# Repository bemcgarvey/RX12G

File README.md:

## RX12G  

Next generation of the RX12 receiver with built in gyro/stabilization  
Can be used with up to 3 DSMX satellite receivers or with any receiver that supports sBus output
(like the FrSky XSR or r-XSR receivers)  

Documentation will appear here once I complete it.

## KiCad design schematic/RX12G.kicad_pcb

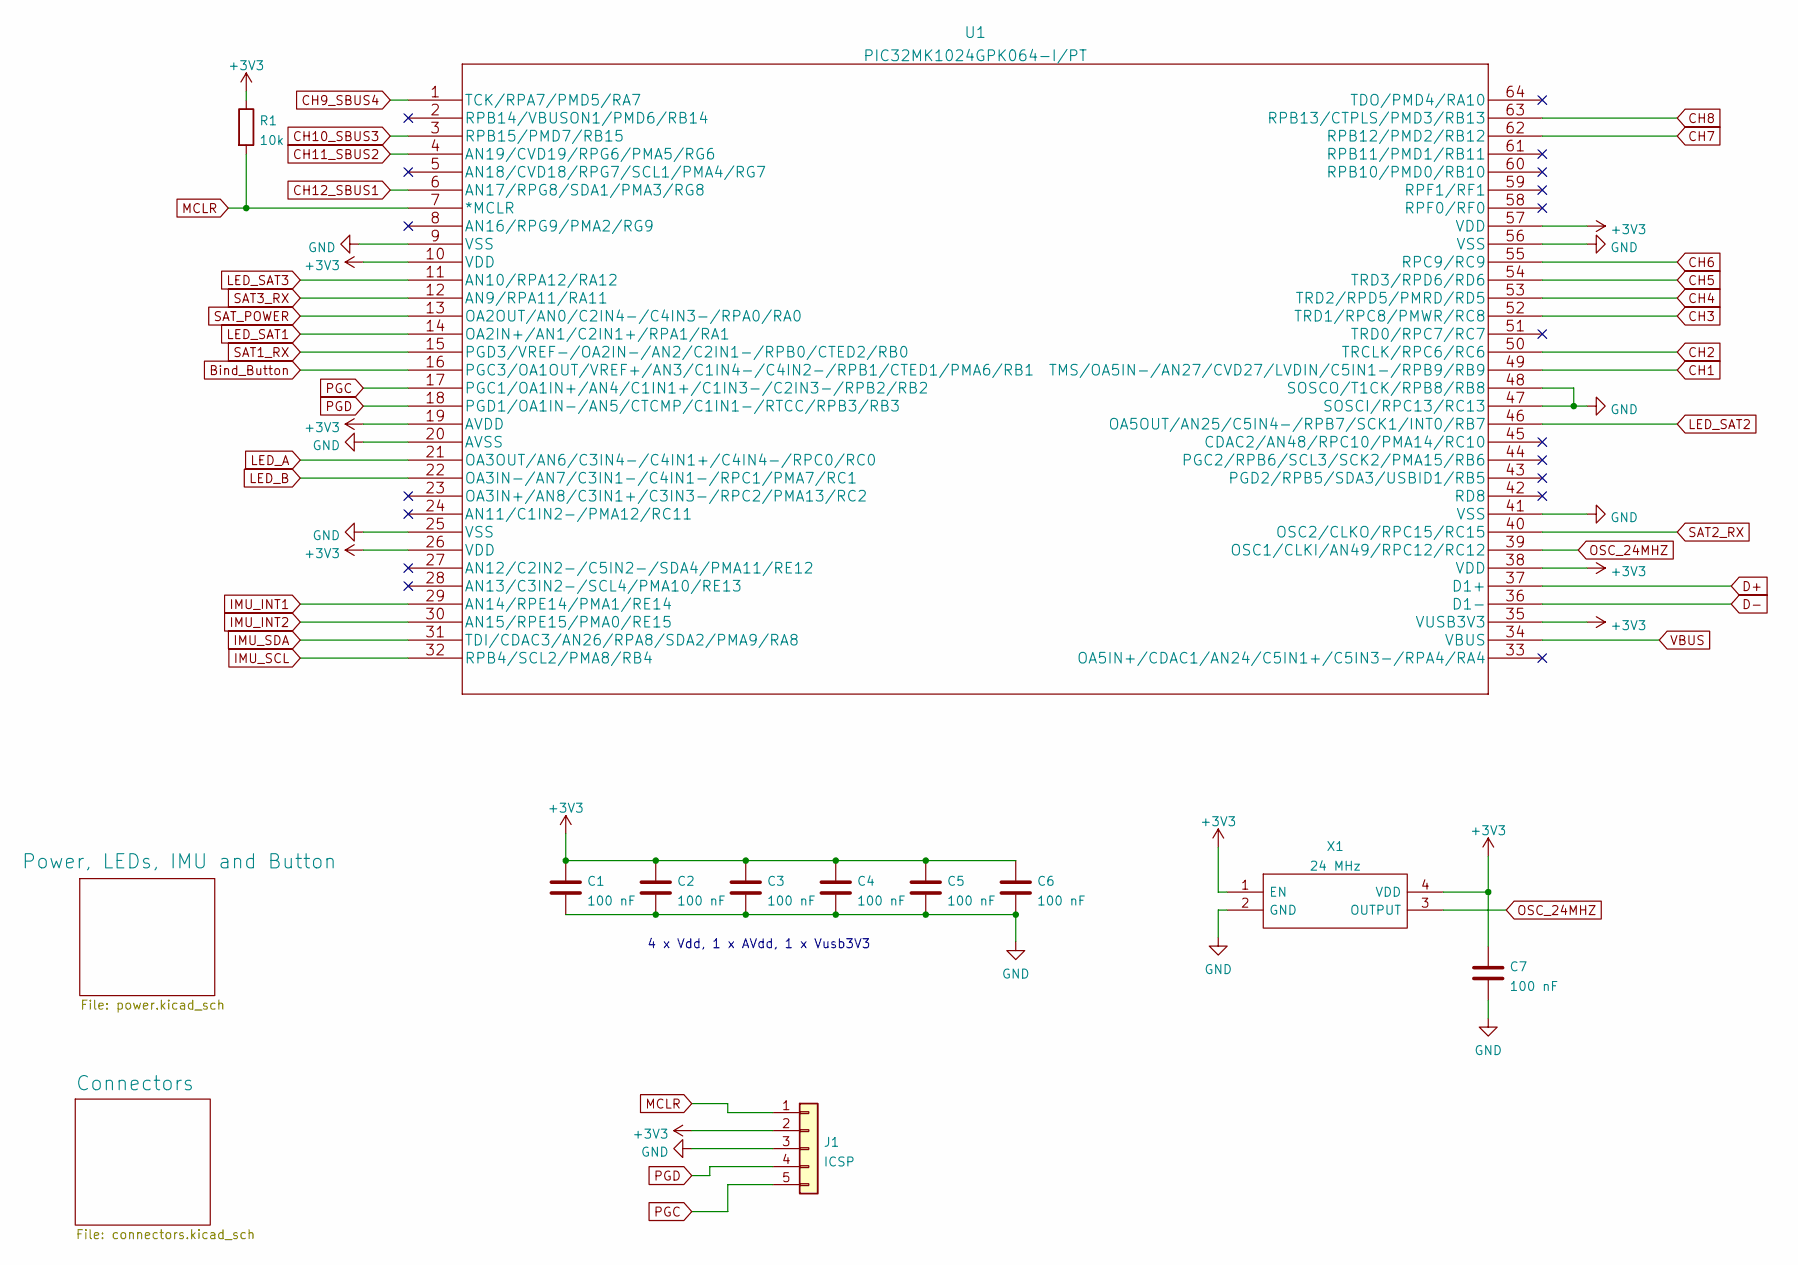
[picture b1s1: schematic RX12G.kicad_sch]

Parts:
C1, C2, C3, C4, C5, C6, C7: 100 nF; C_0402_1005Metric
J1: ICSP; PinHeader_1x05_P2.54mm_Vertical
R1: 10k; R_0603_1608Metric
U1: PIC32MK1024GPK064-I/PT; PIC32MK1024GPK064-I&slash_PT
X1: 24 MHz; ASTMUPCE3312000MHZLJET; Mouser Part Number 815-AMPMAFB-12.0000T

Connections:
+3V3: C1.1, C2.1, C3.1, C4.1, C5.1, C6.1, C7.1, J1.2, R1.1, U1.10 (VDD), U1.19 (AVDD), U1.26 (VDD), U1.35 (VUSB3V3), U1.38 (VDD), U1.57 (VDD), X1.1 (EN), X1.4 (VDD); also elsewhere on the board
Bind_Button: U1.16 (PGC3/OA1OUT/VREF+/AN3/C1IN4-/C4IN2-/RPB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); also elsewhere on the board
CH1: U1.49 (TMS/OA5IN-/AN27/CVD27/LVDIN/C5IN1-/RPB9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); also elsewhere on the board
CH2: U1.50 (TRCLK/RPC6/RC6); also elsewhere on the board
CH3: U1.52 (TRD1/RPC8/PMWR/RC8); also elsewhere on the board
CH4: U1.53 (TRD2/RPD5/PMRD/RD5); also elsewhere on the board
CH5: U1.54 (TRD3/RPD6/RD6); also elsewhere on the board
CH6: U1.55 (RPC9/RC9); also elsewhere on the board
CH7: U1.62 (RPB12/PMD2/RB12); also elsewhere on the board
CH8: U1.63 (RPB13/CTPLS/PMD3/RB13); also elsewhere on the board
CH9_SBUS4: U1.1 (TCK/RPA7/PMD5/RA7); also elsewhere on the board
CH10_SBUS3: U1.3 (RPB15/PMD7/RB15); also elsewhere on the board
CH11_SBUS2: U1.4 (AN19/CVD19/RPG6/PMA5/RG6); also elsewhere on the board
CH12_SBUS1: U1.6 (AN17/RPG8/SDA1/PMA3/RG8); also elsewhere on the board
D+: U1.37 (D1+); also elsewhere on the board
D-: U1.36 (D1-); also elsewhere on the board
GND: C1.2, C2.2, C3.2, C4.2, C5.2, C6.2, C7.2, J1.3, U1.9 (VSS), U1.20 (AVSS), U1.25 (VSS), U1.41 (VSS), U1.47 (SOSCI/RPC13/RC13), U1.48 (SOSCO/T1CK/RPB8/RB8), U1.56 (VSS), X1.2 (GND); also elsewhere on the board
IMU_INT1: U1.29 (AN14/RPE14/PMA1/RE14); also elsewhere on the board
IMU_INT2: U1.30 (AN15/RPE15/PMA0/RE15); also elsewhere on the board
IMU_SCL: U1.32 (RPB4/SCL2/PMA8/RB4); also elsewhere on the board
IMU_SDA: U1.31 (TDI/CDAC3/AN26/RPA8/SDA2/PMA9/RA8); also elsewhere on the board
LED_A: U1.21 (OA3OUT/AN6/C3IN4-/C4IN1+/C4IN4-/RPC0/RC0); also elsewhere on the board
LED_B: U1.22 (OA3IN-/AN7/C3IN1-/C4IN1-/RPC1/PMA7/RC1); also elsewhere on the board
LED_SAT1: U1.14 (OA2IN+/AN1/C2IN1+/RPA1/RA1); also elsewhere on the board
LED_SAT2: U1.46 (OA5OUT/AN25/C5IN4-/RPB7/SCK1/INT0/RB7); also elsewhere on the board
LED_SAT3: U1.11 (AN10/RPA12/RA12); also elsewhere on the board
MCLR: J1.1, R1.2, U1.7 (*MCLR)
OSC_24MHZ: U1.39 (OSC1/CLKI/AN49/RPC12/RC12), X1.3 (OUTPUT)
PGC: J1.5, U1.17 (PGC1/OA1IN+/AN4/C1IN1+/C1IN3-/C2IN3-/RP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)
PGD: J1.4, U1.18 (PGD1/OA1IN-/AN5/CTCMP/C1IN1-/RTCC/RPB3/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)
SAT1_RX: U1.15 (PGD3/VREF-/OA2IN-/AN2/C2IN1-/RPB0/CTED2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); also elsewhere on the board
SAT2_RX: U1.40 (OSC2/CLKO/RPC15/RC15); also elsewhere on the board
SAT3_RX: U1.12 (AN9/RPA11/RA11); also elsewhere on the board
SAT_POWER: U1.13 (OA2OUT/AN0/C2IN4-/C4IN3-/RPA0/RA0); also elsewhere on the board
VBUS: U1.34 (VBUS); also elsewhere on the board

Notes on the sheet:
4 x Vdd, 1 x AVdd, 1 x Vusb3V3

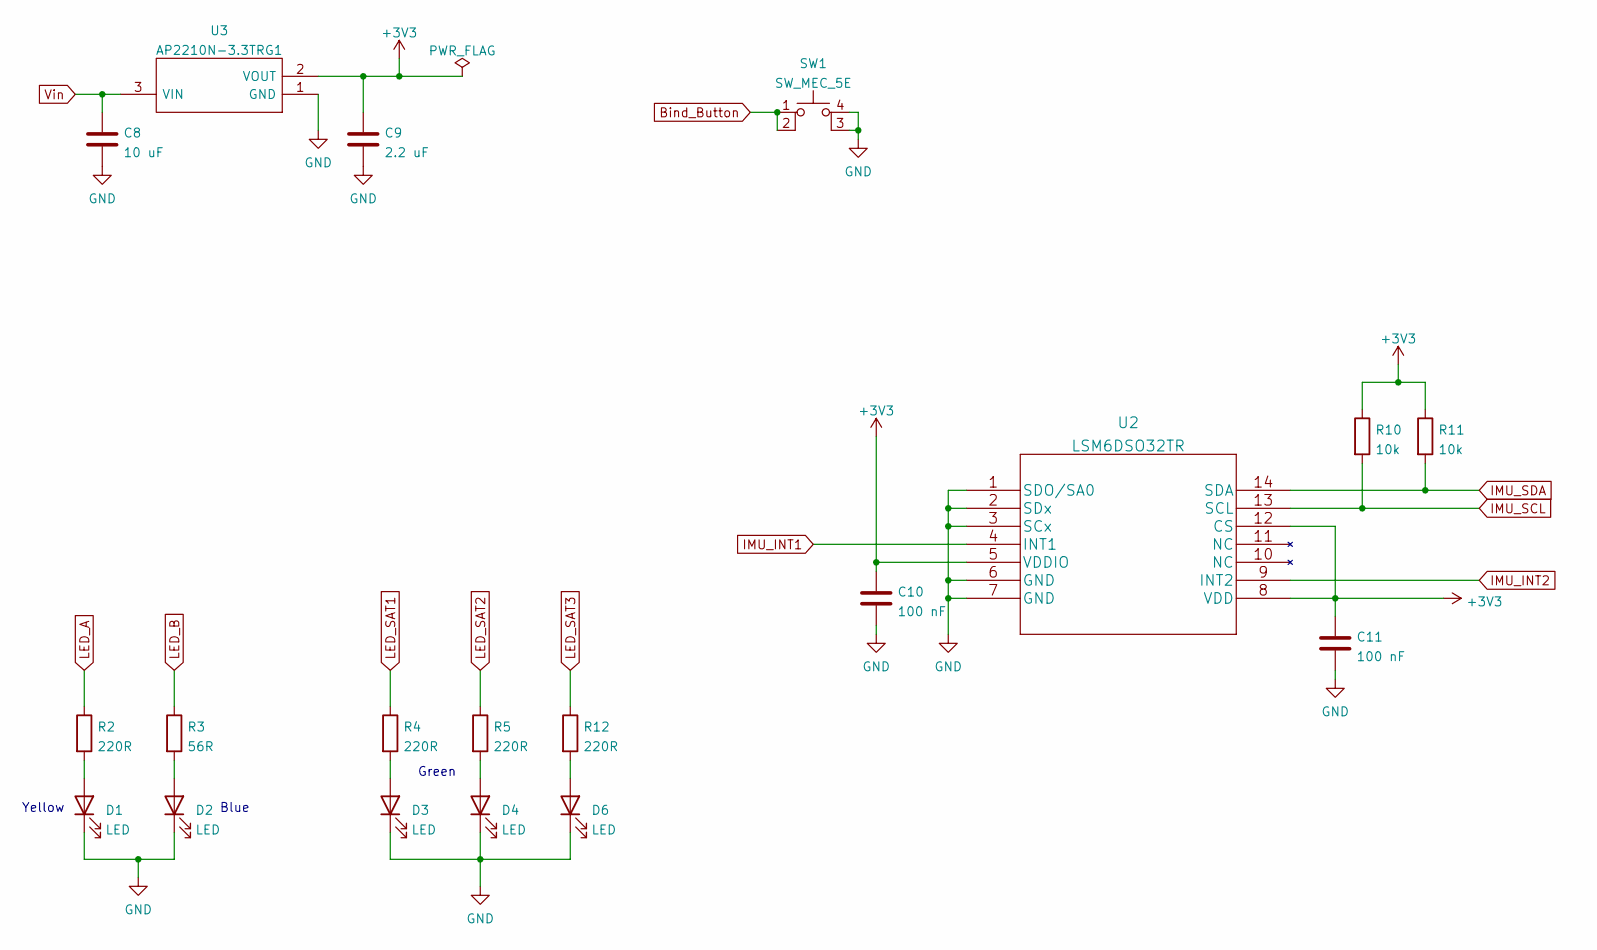
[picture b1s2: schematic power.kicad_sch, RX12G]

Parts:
C8: 10 uF; C_0603_1608Metric
C9: 2.2 uF; C_0603_1608Metric
C10, C11: 100 nF; C_0402_1005Metric
D1, D2, D3, D4, D6: LED; LED_0603_1608Metric
R2, R4, R5, R12: 220R; R_0603_1608Metric
R3: 56R; R_0603_1608Metric
R10, R11: 10k; R_0603_1608Metric
SW1: SW_MEC_5E; PTS647SK38SMTR2LFS
U2: LSM6DSO32TR
U3: AP2210N-3.3TRG1; SOT95P280X145-3N; Mouser Part Number 621-AP2210N-3.3TRG1

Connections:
+3V3: C9.1, C10.1, C11.1, R10.1, R11.1, U2.5 (VDDIO), U2.8 (VDD), U2.12 (CS), U3.2 (VOUT); also elsewhere on the board
Bind_Button: SW1.1, SW1.2; also elsewhere on the board
GND: C8.2, C9.2, C10.2, C11.2, D1.1 (K), D2.1 (K), D3.1 (K), D4.1 (K), D6.1 (K), SW1.3 (K), SW1.4 (A), U2.1 (SDO/SA0), U2.2 (SDx), U2.3 (SCx), U2.6 (GND), U2.7 (GND), U3.1 (GND); also elsewhere on the board
IMU_INT1: U2.4 (INT1); also elsewhere on the board
IMU_INT2: U2.9 (INT2); also elsewhere on the board
IMU_SCL: R10.2, U2.13 (SCL); also elsewhere on the board
IMU_SDA: R11.2, U2.14 (SDA); also elsewhere on the board
LED_A: R2.1; also elsewhere on the board
LED_B: R3.1; also elsewhere on the board
LED_SAT1: R4.1; also elsewhere on the board
LED_SAT2: R5.1; also elsewhere on the board
LED_SAT3: R12.1; also elsewhere on the board
unnamed: D1.2 (A), R2.2
unnamed: D2.2 (A), R3.2
unnamed: D3.2 (A), R4.2
unnamed: D4.2 (A), R5.2
unnamed: D6.2 (A), R12.2
Vin: C8.1, U3.3 (VIN); also elsewhere on the board

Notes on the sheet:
Blue
Yellow
Green

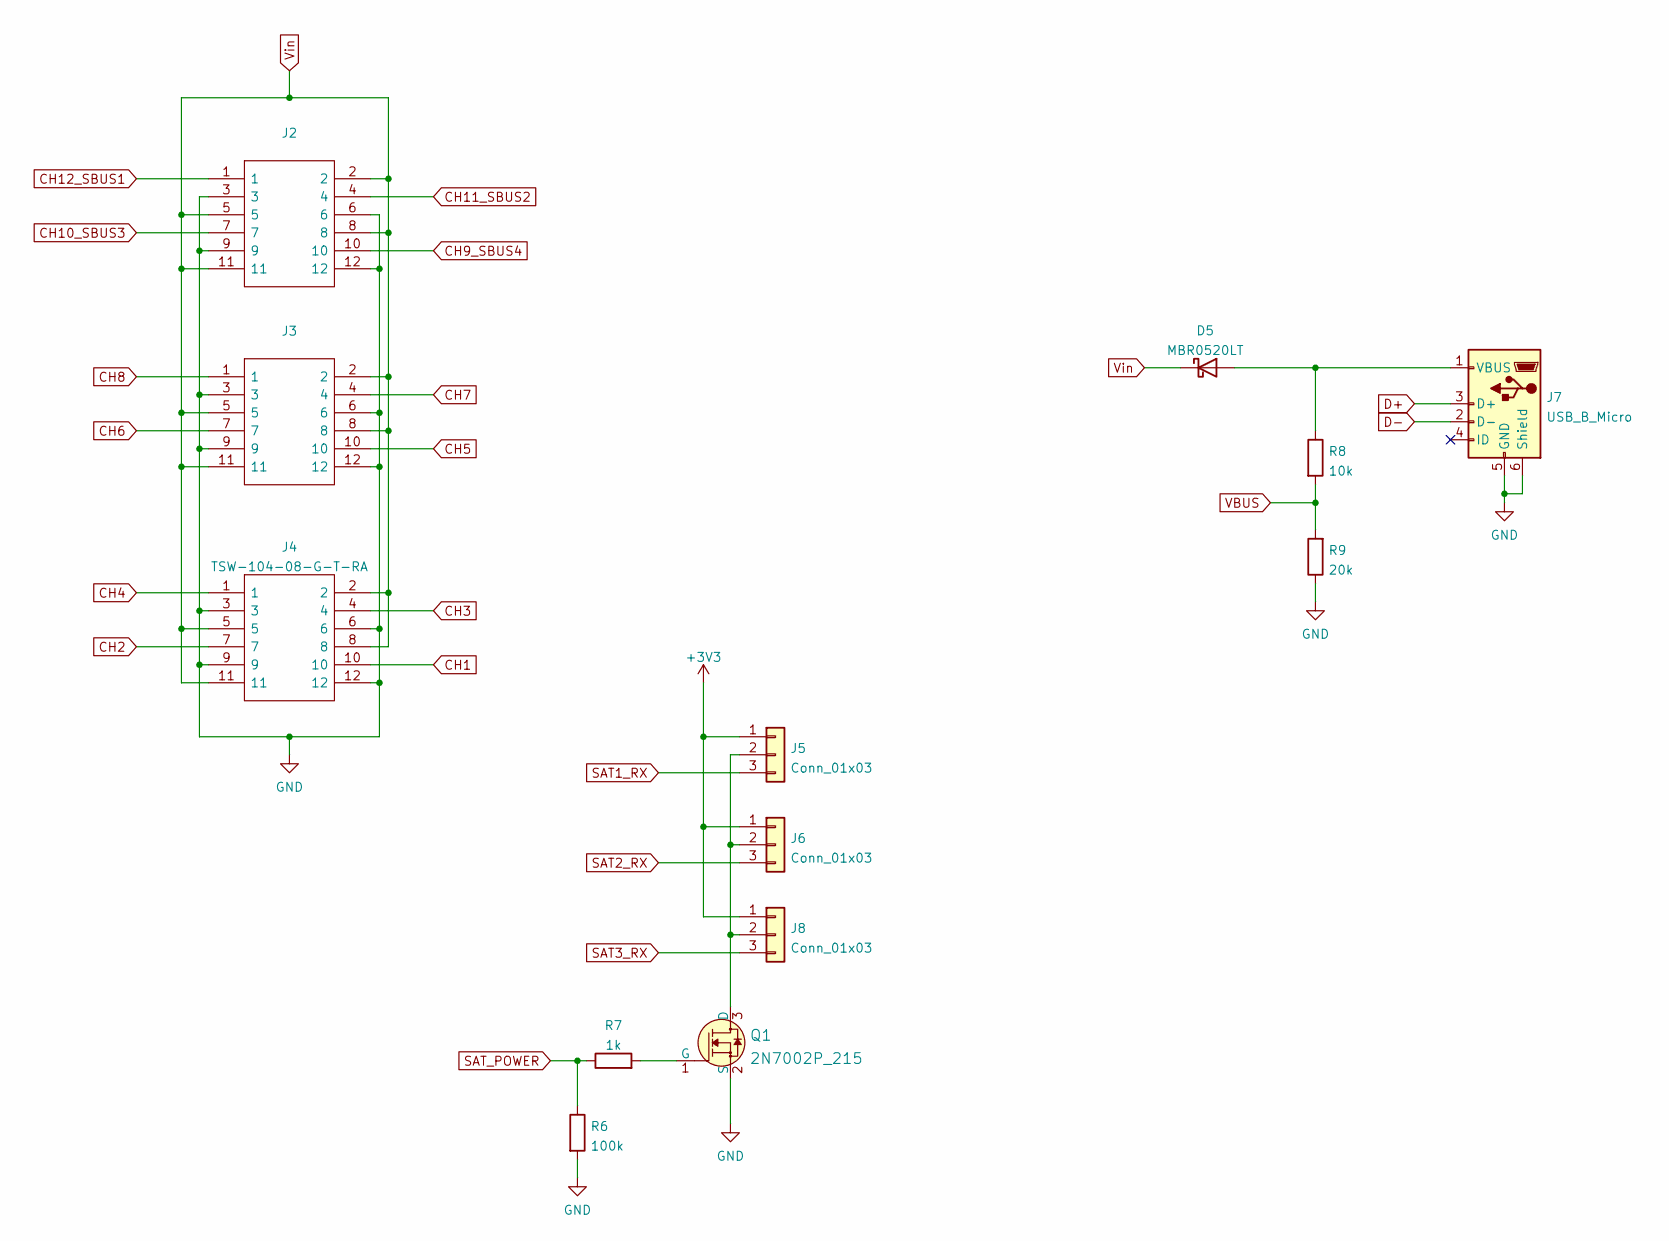
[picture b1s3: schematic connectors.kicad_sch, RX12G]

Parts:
D5: MBR0520LT; D_SOD-123
J2, J3, J4: TSW-104-08-G-T-RA; HDRRA12W64P254_3X4_1016X254X810P; Mouser Part Number 200-TSW10408GTRA
J5, J6, J8: Conn_01x03; JST_ZH_B3B-ZR_1x03_P1.50mm_Vertical
J7: USB_B_Micro; USB_Micro-B_Amphenol_10118194_Horizontal
Q1: 2N7002P_215; SOT-23-3; MPN 2N7002P,215; Digi-Key_PN 1727-4692-1-ND
R6: 100k; R_0603_1608Metric
R7: 1k; R_0603_1608Metric
R8: 10k; R_0603_1608Metric
R9: 20k; R_0603_1608Metric

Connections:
+3V3: J5.1, J6.1, J8.1; also elsewhere on the board
CH1: J4.10; also elsewhere on the board
CH2: J4.7; also elsewhere on the board
CH3: J4.4; also elsewhere on the board
CH4: J4.1; also elsewhere on the board
CH5: J3.10; also elsewhere on the board
CH6: J3.7; also elsewhere on the board
CH7: J3.4; also elsewhere on the board
CH8: J3.1; also elsewhere on the board
CH9_SBUS4: J2.10; also elsewhere on the board
CH10_SBUS3: J2.7; also elsewhere on the board
CH11_SBUS2: J2.4; also elsewhere on the board
CH12_SBUS1: J2.1; also elsewhere on the board
D+: J7.3 (D+); also elsewhere on the board
D-: J7.2 (D-); also elsewhere on the board
GND: J2.3, J2.6, J2.9, J2.12, J3.3, J3.6, J3.9, J3.12, J4.3, J4.6, J4.9, J4.12, J7.5 (GND), J7.6 (Shield), Q1.2 (S), R6.2, R9.1; also elsewhere on the board
unnamed: D5.2 (A), J7.1 (VBUS), R8.1
unnamed: J5.2, J6.2, J8.2, Q1.3 (D)
unnamed: Q1.1 (G), R7.2
SAT1_RX: J5.3; also elsewhere on the board
SAT2_RX: J6.3; also elsewhere on the board
SAT3_RX: J8.3; also elsewhere on the board
SAT_POWER: R6.1, R7.1; also elsewhere on the board
VBUS: R8.2, R9.2; also elsewhere on the board
Vin: D5.1 (K), J2.2, J2.5, J2.8, J2.11, J3.2, J3.5, J3.8, J3.11, J4.2, J4.5, J4.8, J4.11; also elsewhere on the board

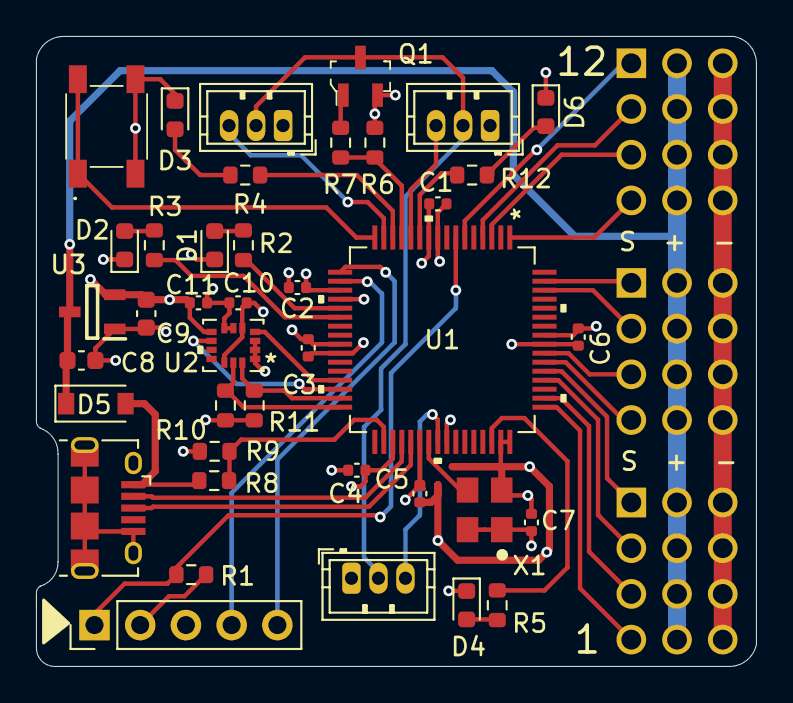
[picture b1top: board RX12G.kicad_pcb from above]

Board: 4 copper layers, 40.0 x 35.0 mm, 43 parts (0 on the bottom side), 44 nets.

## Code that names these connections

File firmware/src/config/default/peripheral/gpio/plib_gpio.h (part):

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#define SAT3_LED_Get()               ((PORTA >> 12) & 0x1)
#define SAT3_LED_PIN                  GPIO_PIN_RA12

/*** Macros for SAT3_RX pin ***/
#define SAT3_RX_Get()               ((PORTA >> 11) & 0x1)
#define SAT3_RX_PIN                  GPIO_PIN_RA11

/*** Macros for SAT_POWER pin ***/
#define SAT_POWER_Set()               (LATASET = (1<<0))
#define SAT_POWER_Clear()             (LATACLR = (1<<0))
#define SAT_POWER_Toggle()            (LATAINV= (1<<0))
#define SAT_POWER_OutputEnable()      (TRISACLR = (1<<0))
#define SAT_POWER_InputEnable()       (TRISASET = (1<<0))
#define SAT_POWER_Get()               ((PORTA >> 0) & 0x1)
#define SAT_POWER_PIN                  GPIO_PIN_RA0

/*** Macros for SAT1_LED pin ***/
#define SAT1_LED_Set()               (LATASET = (1<<1))
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#define SAT1_LED_Get()               ((PORTA >> 1) & 0x1)
#define SAT1_LED_PIN                  GPIO_PIN_RA1

/*** Macros for SAT1_RX pin ***/
#define SAT1_RX_Get()               ((PORTB >> 0) & 0x1)
#define SAT1_RX_PIN                  GPIO_PIN_RB0

/*** Macros for BIND_BUTTON pin ***/
#define BIND_BUTTON_Get()               ((PORTB >> 1) & 0x1)
#define BIND_BUTTON_PIN                  GPIO_PIN_RB1

/*** Macros for LED_A pin ***/
#define LED_A_Set()               (LATCSET = (1<<0))
#define LED_A_Clear()             (LATCCLR = (1<<0))
#define LED_A_Toggle()            (LATCINV= (1<<0))
#define LED_A_OutputEnable()      (TRISCCLR = (1<<0))
#define LED_A_InputEnable()       (TRISCSET = (1<<0))
#define LED_A_Get()               ((PORTC >> 0) & 0x1)
#define LED_A_PIN                  GPIO_PIN_RC0

/*** Macros for LED_B pin ***/
#define LED_B_Set()               (LATCSET = (1<<1))
#define LED_B_Clear()             (LATCCLR = (1<<1))
#define LED_B_Toggle()            (LATCINV= (1<<1))
#define LED_B_OutputEnable()      (TRISCCLR = (1<<1))
#define LED_B_InputEnable()       (TRISCSET = (1<<1))
#define LED_B_Get()               ((PORTC >> 1) & 0x1)
#define LED_B_PIN                  GPIO_PIN_RC1

/*** Macros for IMU_INT1 pin ***/
#define IMU_INT1_Get()               ((PORTE >> 14) & 0x1)
#define IMU_INT1_PIN                  GPIO_PIN_RE14

/*** Macros for IMU_INT2 pin ***/
#define IMU_INT2_Get()               ((PORTE >> 15) & 0x1)
#define IMU_INT2_PIN                  GPIO_PIN_RE15

/*** Macros for SAT2_RX pin ***/
#define SAT2_RX_Get()               ((PORTC >> 15) & 0x1)
#define SAT2_RX_PIN                  GPIO_PIN_RC15

/*** Macros for SAT2_LED pin ***/
#define SAT2_LED_Set()               (LATBSET = (1<<7))
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
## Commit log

2022-04-25 Created KiCad project
2022-04-27 Partial schematic
2022-04-29 Harmony project created - pin assignment only
2022-04-29 Complete schematic
2022-04-29 Initial pcb with design rules
2022-04-29 Initial pcb layout - footprints only
2022-04-29 Workable pcb layout
    Needs work on silkscreen
2022-04-29 Improved board ouline
2022-04-29 Generated BOM, added gerber settings
2022-04-30 Fixed missing SAT_POWER connection
    Also re-assigned some pins to improve pcb layout
2022-04-30 Rounded outline corners at usb connector
2022-04-30 Repositioned some components
    Moved sat leds, hid the connector labels
2022-05-01 Minor fixes.
    D6 footprint, updated BOM
2022-05-01 Some minor silkscreen fixes
2022-05-01 Changed R3 value and some minor track adjustments
2022-05-02 Generated gerbers
2022-05-19 Simple Harmony project - code is running
2022-05-19 With I2C test code
2022-05-19 With RTOS
2022-05-19 Sat power tested
2022-05-20 Clean start - system timer running
2022-05-21 Bind working
2022-05-21 UART DMA working
2022-05-21 Improved DMA
2022-05-21 All satellites working
2022-05-22 PWM outputs working
2022-05-22 Bind button task working
2022-05-23 Passthrough mode working
    Still needs failsafe detection.
2022-05-24 Eliminated extra queue - better sequence for passthrough
2022-05-24 Normal failsafe working
    Improved channel enable
2022-05-24 Settings working
2022-05-24 Added status leds
2022-05-25 Added S.Bus output
2022-05-25 Improved led task
2022-05-25 Fixed spurious channel bug
2022-05-26 Added firmware version
2022-05-27 USB enumerates
2022-05-27 Initial Qt project
2022-05-27 Revert "Initial Qt project"
    This reverts commit 72e322c37bd2a0aa7e445bbf03dcde9e7fa22cd5.
2022-05-27 Initial Qt project using qmake and Qt 6
2022-05-27 Simple usb communication working
2022-05-27 usb send and receive working
2022-05-28 Cleaned up comments
2022-05-28 Improved usb task structure
2022-05-28 More usb functionality
2022-05-28 Load and Save settings working
2022-05-28 Fixed settings bug
2022-05-29 Channel display working
2022-05-30 Preset failsafe working
    Fixed bug where failsafe values were being overwritten
2022-05-30 getChannels timer turned off when on another tab
2022-05-30 IMU communication working
2022-05-30 Reading acceleration correctly
    Fixed bug where ExtInt2 was too high a priority for a FreeRTOS API call
2022-05-31 Working on UI
2022-05-31 Gyro and accel working
2022-05-31 More UI improvements
2022-05-31 Full settings
2022-06-01 More settings UI
2022-06-01 More settings and UI additions
2022-06-01 Increased usb wait time
    Hopefully prevents occasional save errors
2022-06-01 Added icon and fixed menu issue
2022-06-02 Added version and file open/save
2022-06-02 Fixed bug caused by hidWatcher having a parent
2022-06-02 All settings displayed and saved
2022-06-02 Added reboot
2022-06-03 Added some validity checks and UI improvements
2022-06-03 Added sensor display UI elements
2022-06-04 Flight mode select working
    Basic gain setting and calculation
2022-06-04 Added "Actual gain" display to client
2022-06-04 Increased freeRTOS heap size and gyroTask stack size
2022-06-04 Added gyro offset calibration and imuReady signal
2022-06-05 Level calibration working
2022-06-06 gyroTask framework in place
2022-06-07 Improved sensor display
2022-06-07 Working on attitude
2022-06-08 Attitude seems to be working
    Still needs work to handle different hardware orientations
2022-06-08 Changed servo update method
    Only update servo positions after positions have been sent to outputs.
2022-06-09 Autolevel is functioning
    But still needs some work
2022-06-09 My attitude algorithm working
    Ready to branch
2022-06-10 Fusion working
2022-06-10 Removed unused code.
2022-06-10 Remapped axes.
2022-06-10 Mapped axes correctly. Fusion working well.
2022-06-10 All orientations mapped.
2022-06-11 Improved gyro calibration
2022-06-12 Added new blink options
2022-06-12 Added aileron/elevator wiggle when imu ready
    Also fixed the output limit checks
    Put calibration time back to 2 sec.
2022-06-13 Created bootloader config with linker script
    Changed clock settings and some other config bits.
    Using newest Harmony libs.
2022-06-13 Added bootloader
2022-06-13 Finalized pmd and handled imu failure modes
2022-06-13 Changed upper channel offsets to allow for 200Hz rate
2022-06-16 Revert "Changed upper channel offsets to allow for 200Hz rate"
    This reverts commit d4eb5f1dcffb48557b9e3866d52f74f4f5c5acf6.
2022-06-16 Revert "Finalized pmd and handled imu failure modes"
    This reverts commit 8459ccad66629b4c4f65116186b16cd6f5d56a7b.
2022-06-16 Finalized pmd and locked it.
2022-06-16 Reversed pitch adjustment when inverted.
    Removed timing code from updateAttitude. It was overriding the zSign value.
2022-06-16 Handled some imu failure modes
2022-06-16 Added Launch Assist functions
2022-06-17 Fixed level correction for different orientations
2022-06-19 Normal mode beginning to work
2022-06-19 Working better
2022-06-20 All axes for normal mode
2022-06-22 Normal mode ready to test
2022-06-22 Added elevon settings plus some minor fixes and clean up
2022-06-22 Added firmware update tab
    Added software trigger to bootloader and firmware
2022-06-22 Some comments removed/added
2022-06-25 Added stubs for trainer and attitude lock
    Also added custom modes and some minor fixes
2022-06-25 Changed bootloader folder to keep MHC happy and some minor tweaks
    Turned on all LEDs in bootload mode.
    Added a 2 second delay on the button
2022-06-25 Added ypr display to sensor tab
2022-06-25 Initial attitude lock code
2022-06-27 Eliminated duplicate variables
2022-06-28 Better attitude lock
2022-06-28 Added watchdog timer
2022-07-02 Made wiggle faster
2022-07-02 Added adjustment to pitch correction based on roll
2022-07-04 Fixed button bounce problem and WDT when entering bind mode.
2022-07-05 Fixed some errors in pitch code
2022-09-10 Started trainer mode
2022-09-11 Added rxOnly mode
    Also fixed offsets on upper channels to allow up to 200Hz servo rate.
2022-09-15 Changed USB detection method
    Now will detect USB plugged in at any time, not just at power on.
2022-09-15 Wiggle only active controls on start
2022-09-15 Fixed reboot bug
    Servos were going out of range sometimes. Added a process to shut off outputs before restart.
2022-09-16 Fixed pitch autolevel bug
2022-09-17 Improved output timing
    Also added key to prevent accidental output disable
2022-09-17 Removed extra condition in sticksCentered
2022-09-17 Improved gain settings
    Now has separate gains for level, lock and normal modes
2022-09-18 Stubbed in AETR channel order
    Not yet implemented
2022-09-19 Implemented TAER/AETR channel ordering
    AETR still needs to be tested.
    Fixed error in attitudeLock.c where AILERON was used instead of RUDDER.
    Fixed wiggle timing to use control loop freq
2022-09-20 Trainer mode coded.
    Some comment updates
2022-09-25 Added bind via usb connection
2022-09-27 Fixed yaw gain channel bug
2022-09-30 Fixed XPlus channels bug
2022-09-30 Fixed phase bit handling
2022-09-30 Added upper channels display
2022-10-04 Better initialization of autolevel
2022-10-04 Working dcm code
2022-10-05 Improved dcm init
2022-10-05 removed zSign - not needed
2022-10-05 Working dcm algorithm
2022-10-05 Removed zSign
2022-10-10 Added some TODOs
2022-10-10 Removed unused files
2022-10-11 Improved output setting.
    Also fixed an elevator2 bug and limits tab in UI
2022-10-12 Improved attitude lock mode
2022-10-14 Changed trainer mode algorithm
2022-10-14 Stubbed in angle mode
2022-10-15 Angle mode functions
2022-10-17 Changed save file format to json
2022-10-22 Fixed bug when a gyro axis is reversed
2022-10-27 Added S.Bus satellite option
2022-10-29 Added elevon functions
2022-10-29 Added a minimum gain for trainer and angle mode.
2022-10-30 Fixed baud rate. Changed satellite detection for SBus
    Still a bug with SAT3
2022-10-30 Fixed UART error interrupt bug
2022-10-31 SBus satellites are now detected correctly
2022-10-31 Added missing file comment headers
2022-11-01 Added nmi handler to bootloader to handle clock failure
2022-11-01 Fixed missing lines in gyro display bars and min-max bars
2022-11-03 Discarded first DSMX packet
    The first packet from the satellite had invalid channel 11 or 12 data sometimes.
2022-11-03 Small UI improvement
2022-11-04 Added About dialog
2022-11-04 Set some size constraints
2022-11-25 Added some default PID values
2023-08-28 Minor gain adjustments
    Default values.
    Decreased motion sensitivity
2023-08-30 Improved imu initialization
    Moved init function to task
2023-08-30 Moved task priorities to header
2023-08-30 Minor UI fixes
2024-01-03 Fixed bug in bindSats function
2024-01-03 Added change log
    Also updated compiler version - now tested with XC32 4.35
2025-07-03 Update pcb to KiCad 9
2025-07-04 Receive working
    Still need telemetry
2025-07-05 Telemetry working
2025-07-05 Updated client for ELRS option

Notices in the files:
firmware/src/config/default/peripheral/gpio/plib_gpio.h:
Copyright (C) 2019 Microchip Technology Inc. and its subsidiaries.
parts and their libraries:
Copyright 2021 Accelerated Designs. All rights reserved.
